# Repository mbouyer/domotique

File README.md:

# domotique
gestion du chauffage et aération d'une habitation

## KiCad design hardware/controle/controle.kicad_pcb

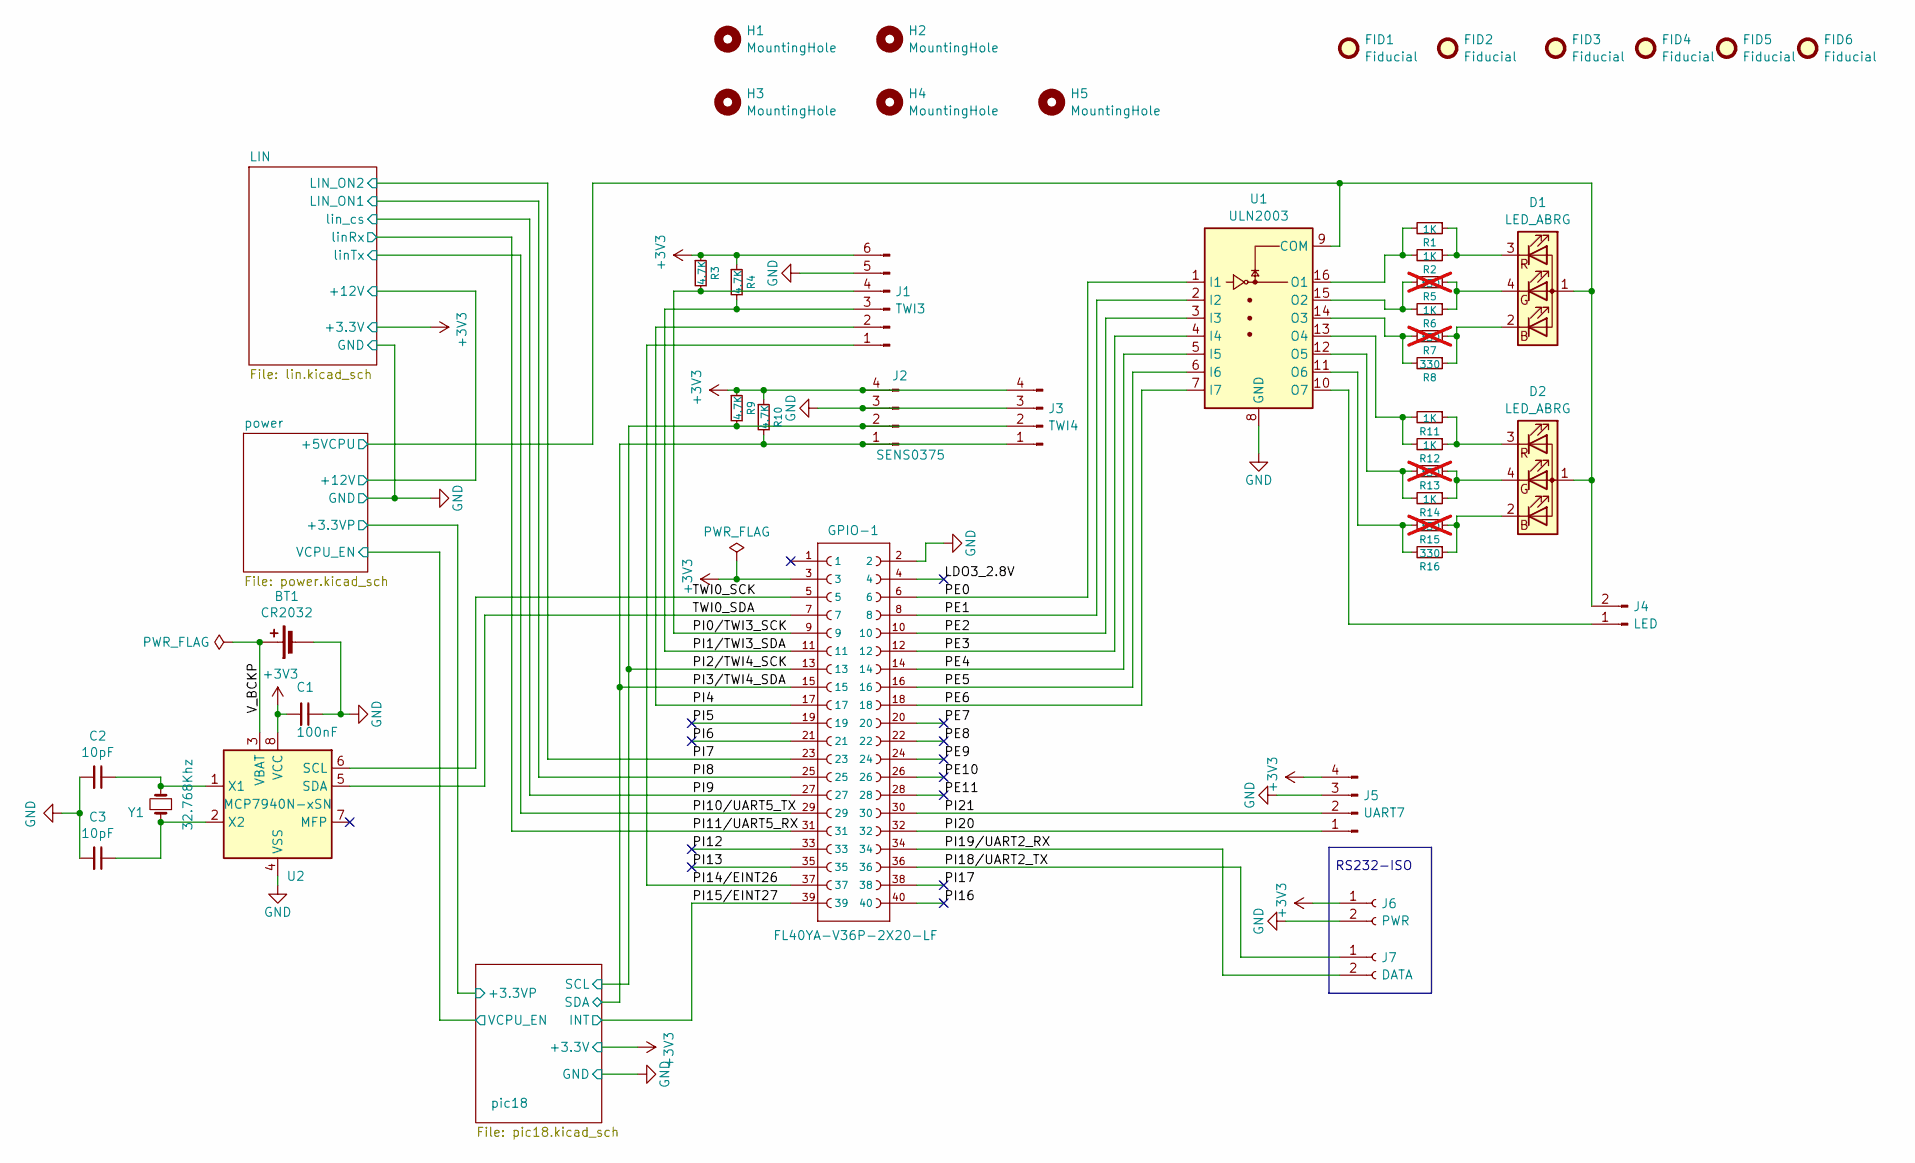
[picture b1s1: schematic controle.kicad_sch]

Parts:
BT1: CR2032; 1066
C1: 100nF; C_0603_1608Metric_Pad1.08x0.95mm_HandSolder
C2, C3: 10pF; C_0603_1608Metric_Pad1.08x0.95mm_HandSolder
D1, D2: LED_ABRG; LED MP001251
FID1, FID2, FID3, FID4, FID5, FID6: Fiducial; Fiducial_1mm_Mask2mm
GPIO-1: FL40YA-V36P-2X20-LF; A10_OLIMEXINO_LIME_SHIELD_1-YA-V36P-2X20-LF
H1, H2, H3, H4, H5: MountingHole; MountingHole_3.2mm_M3
J1: TWI3; PinHeader_1x06_P2.54mm_Vertical
J2: SENS0375; PinHeader_1x04_P2.54mm_Vertical
J3: TWI4; PinHeader_1x04_P2.54mm_Vertical
J4: LED; PinHeader_1x02_P2.54mm_Vertical
J5: UART7; PinHeader_1x04_P2.54mm_Vertical
J6: PWR; PinSocket_1x02_P2.54mm_Vertical
J7: DATA; PinSocket_1x02_P2.54mm_Vertical
R1, R2, R6, R11, R12, R14: 1K; R_0805_2012Metric_Pad1.20x1.40mm_HandSolder
R3, R4, R9, R10: 4.7K; R_0805_2012Metric_Pad1.20x1.40mm_HandSolder
R5, R7, R13, R15: 330; R_0805_2012Metric_Pad1.20x1.40mm_HandSolder; not fitted
R8, R16: 330; R_0805_2012Metric_Pad1.20x1.40mm_HandSolder
U1: ULN2003; SOIC-16_3.9x9.9mm_P1.27mm
U2: MCP7940N-xSN; SOIC-8_3.9x4.9mm_P1.27mm
Y1: 32.768Khz; CMR200T

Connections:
+3V3: C1.2, GPIO-1.3, J1.6, J2.4, J3.4, J5.4, J6.1, R3.1, R4.1, R9.1, R10.1, U2.8 (VCC); also elsewhere on the board
/LDO3_2.8V: GPIO-1.4
/PE0: GPIO-1.6, U1.1 (I1)
/PE1: GPIO-1.8, U1.2 (I2)
/PE2: GPIO-1.10, U1.3 (I3)
/PE3: GPIO-1.12, U1.4 (I4)
/PE4: GPIO-1.14, U1.5 (I5)
/PE5: GPIO-1.16, U1.6 (I6)
/PE6: GPIO-1.18, U1.7 (I7)
/PE7: GPIO-1.20
/PE8: GPIO-1.22
/PE9: GPIO-1.24
/PE10: GPIO-1.26
/PE11: GPIO-1.28
/PI0/TWI3_SCK: GPIO-1.9, J1.4, R3.2
/PI1/TWI3_SDA: GPIO-1.11, J1.3, R4.2
/PI2/TWI4_SCK: GPIO-1.13, J2.2, J3.2, R9.2; also elsewhere on the board
/PI3/TWI4_SDA: GPIO-1.15, J2.1, J3.1, R10.2; also elsewhere on the board
/PI4: GPIO-1.17, J1.2
/PI5: GPIO-1.19
/PI6: GPIO-1.21
/PI7: GPIO-1.23; also elsewhere on the board
/PI8: GPIO-1.25; also elsewhere on the board
/PI9: GPIO-1.27; also elsewhere on the board
/PI10/UART5_TX: GPIO-1.29; also elsewhere on the board
/PI11/UART5_RX: GPIO-1.31; also elsewhere on the board
/PI12: GPIO-1.33
/PI13: GPIO-1.35
/PI14/EINT26: GPIO-1.37, J1.1
/PI15/EINT27: GPIO-1.39; also elsewhere on the board
/PI16: GPIO-1.40
/PI17: GPIO-1.38
/PI18/UART2_TX: GPIO-1.36, J7.1
/PI19/UART2_RX: GPIO-1.34, J7.2
/PI20: GPIO-1.32, J5.1
/PI21: GPIO-1.30, J5.2
/TWI0_SCK: GPIO-1.5, U2.6 (SCL)
/TWI0_SDA: GPIO-1.7, U2.5 (SDA)
/V_BCKP: BT1.1 (+), U2.3 (VBAT)
/power/+5VCPU: D1.1 (A), D2.1 (A), J4.2, U1.9 (COM); also elsewhere on the board
GND: BT1.2 (-), C1.1, C2.2, C3.2, GPIO-1.2, J1.5, J2.3, J3.3, J5.3, J6.2, U1.8 (GND), U2.4 (VSS); also elsewhere on the board
unnamed: D1.2 (BK), R7.1, R8.1
unnamed: D1.4 (GK), R5.1, R6.1
unnamed: D1.3 (RK), R1.1, R2.1
unnamed: D2.2 (BK), R15.1, R16.1
unnamed: D2.4 (GK), R13.1, R14.1
unnamed: D2.3 (RK), R11.1, R12.1
unnamed: J4.1, U1.10 (O7)
unnamed: R1.2, R2.2, U1.16 (O1)
unnamed: R5.2, R6.2, U1.15 (O2)
unnamed: R7.2, R8.2, U1.14 (O3)
unnamed: R11.2, R12.2, U1.13 (O4)
unnamed: R13.2, R14.2, U1.12 (O5)
unnamed: R15.2, R16.2, U1.11 (O6)
unnamed: C2.1, U2.1 (X1), Y1.2
unnamed: C3.1, U2.2 (X2), Y1.1

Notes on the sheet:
RS232-ISO

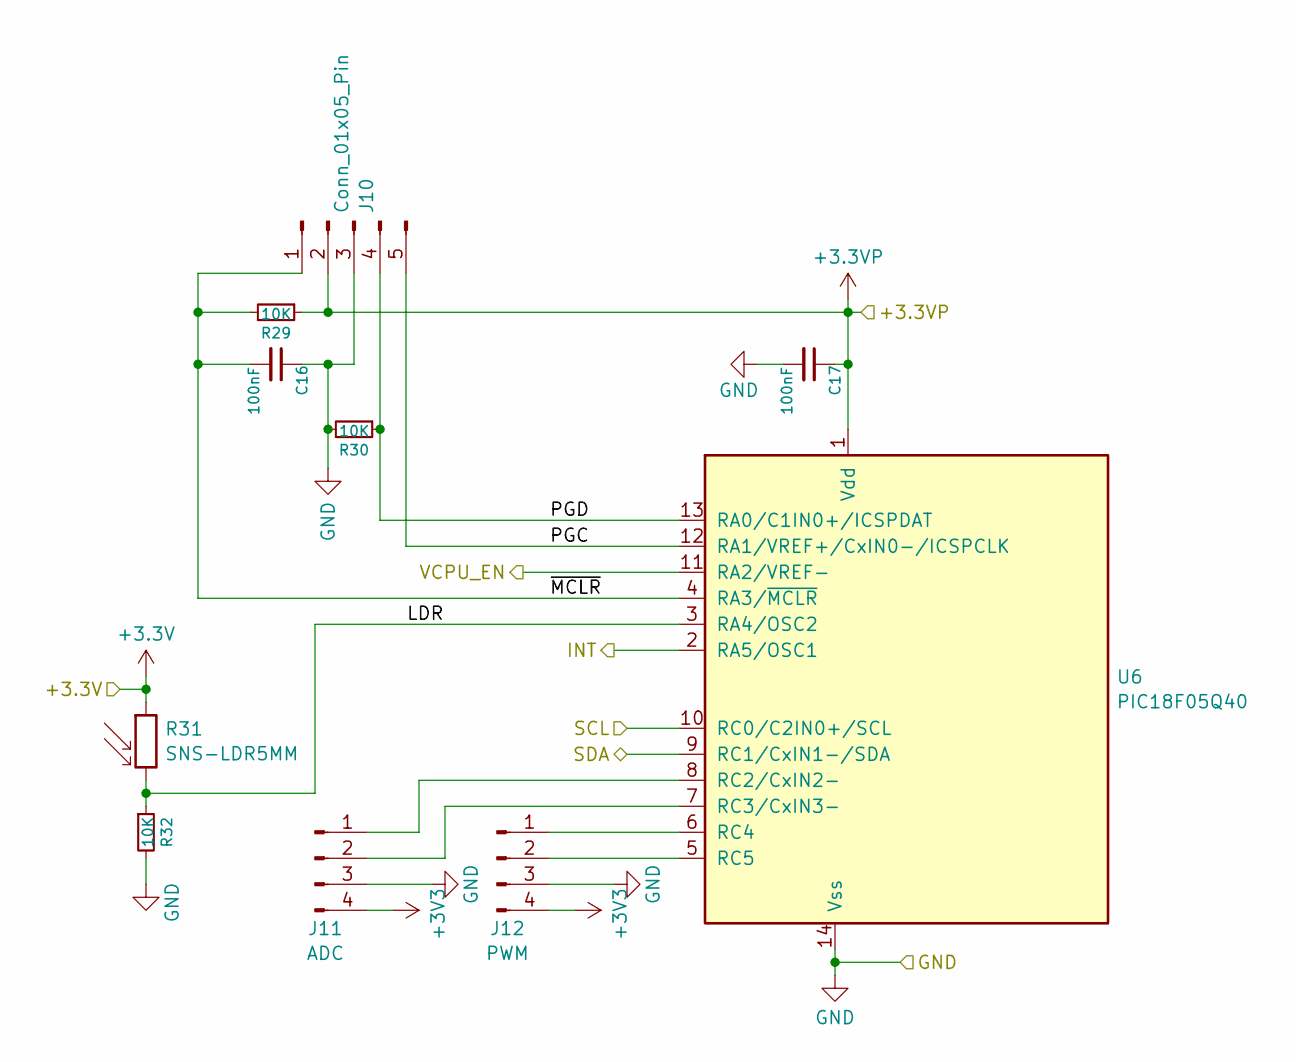
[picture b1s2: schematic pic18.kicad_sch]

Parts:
C16, C17: 100nF; C_0603_1608Metric_Pad1.08x0.95mm_HandSolder
J10: Conn_01x05_Pin; PinHeader_1x05_P2.54mm_Horizontal
J11: ADC; PinHeader_1x04_P2.54mm_Vertical
J12: PWM; PinHeader_1x04_P2.54mm_Vertical
R29, R30, R32: 10K; R_0805_2012Metric_Pad1.20x1.40mm_HandSolder
R31: SNS-LDR5MM; R_LDR_5.0x4.1mm_P3mm_Vertical
U6: PIC18F05Q40; SOIC-14_3.9x8.7mm_P1.27mm

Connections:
+3.3VP: C17.1, J10.2, R29.1, U6.1 (Vdd); also elsewhere on the board
+3V3: J11.4, J12.4, R31.1; also elsewhere on the board
/PI2/TWI4_SCK: U6.10 (RC0/C2IN0+/SCL); also elsewhere on the board
/PI3/TWI4_SDA: U6.9 (RC1/CxIN1-/SDA); also elsewhere on the board
/PI15/EINT27: U6.2 (RA5/OSC1); also elsewhere on the board
/pic18/LDR: R31.2, R32.1, U6.3 (RA4/OSC2)
/pic18/PGC: J10.5, U6.12 (RA1/VREF+/CxIN0-/ICSPCLK)
/pic18/PGD: J10.4, R30.1, U6.13 (RA0/C1IN0+/ICSPDAT)
/pic18/VCPU_EN: U6.11 (RA2/VREF-); also elsewhere on the board
/pic18/~MCLR: C16.2, J10.1, R29.2, U6.4 (RA3/~MCLR)
GND: C16.1, C17.2, J10.3, J11.3, J12.3, R30.2, R32.2, U6.14 (Vss); also elsewhere on the board
unnamed: J11.1, U6.8 (RC2/CxIN2-)
unnamed: J11.2, U6.7 (RC3/CxIN3-)
unnamed: J12.1, U6.6 (RC4)
unnamed: J12.2, U6.5 (RC5)

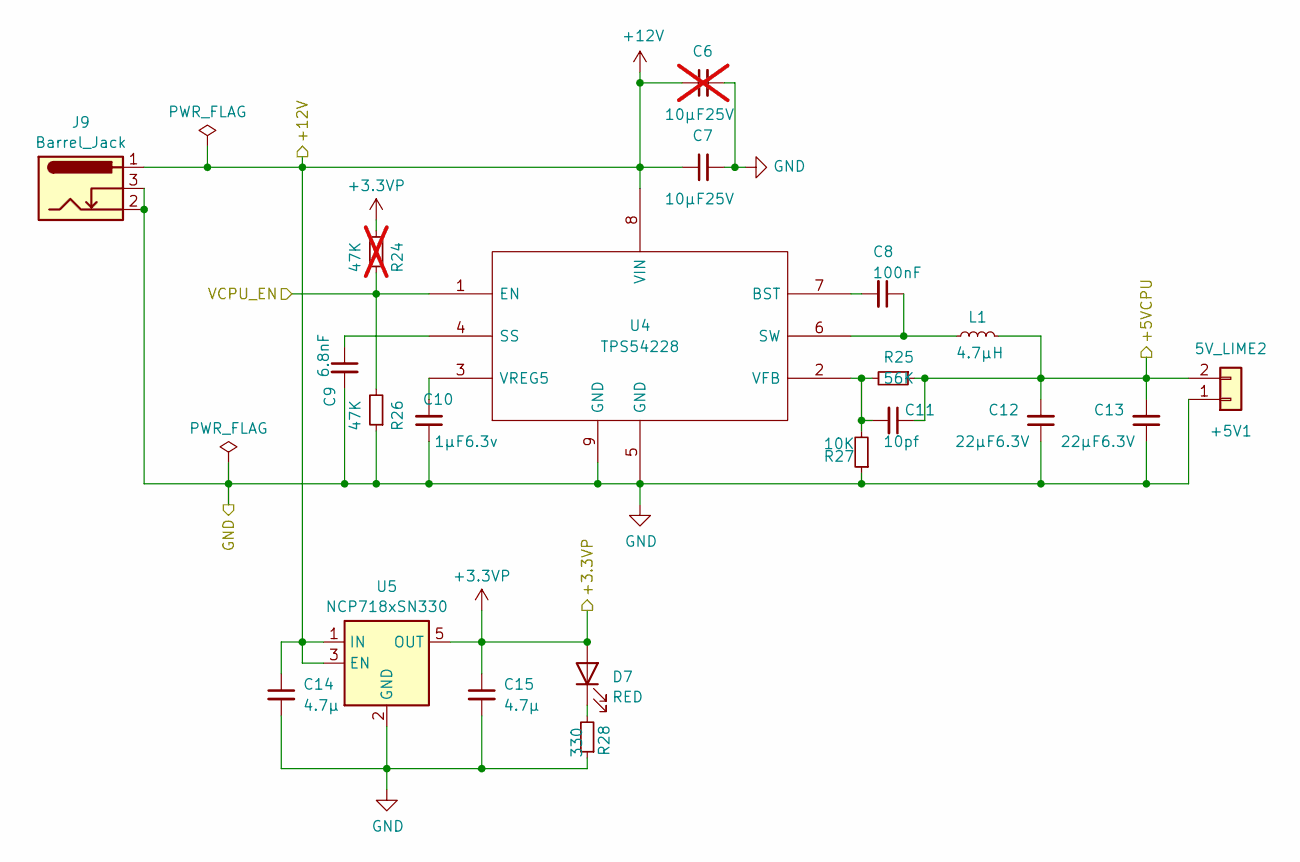
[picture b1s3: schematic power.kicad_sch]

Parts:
+5V1: 5V_LIME2; MC24356
C6: 10µF25V; C_1210_3225Metric_Pad1.33x2.70mm_HandSolder; not fitted
C7: 10µF25V; C_1210_3225Metric_Pad1.33x2.70mm_HandSolder
C8: 100nF; C_0603_1608Metric_Pad1.08x0.95mm_HandSolder
C9: 6.8nF; C_0603_1608Metric_Pad1.08x0.95mm_HandSolder
C10: 1µF6.3v; C_0603_1608Metric_Pad1.08x0.95mm_HandSolder
C11: 10pf; C_0603_1608Metric_Pad1.08x0.95mm_HandSolder
C12, C13: 22µF6.3V; C_1210_3225Metric_Pad1.33x2.70mm_HandSolder
C14, C15: 4.7µ; C_0805_2012Metric_Pad1.18x1.45mm_HandSolder
D7: RED; LED_0805_2012Metric
J9: Barrel_Jack; BarrelJack_Wuerth_6941xx301002
L1: 4.7µH; L_TT_7.3x6.8
R24: 47K; R_0805_2012Metric_Pad1.20x1.40mm_HandSolder; not fitted
R25: 56K; R_0805_2012Metric_Pad1.20x1.40mm_HandSolder
R26: 47K; R_0805_2012Metric_Pad1.20x1.40mm_HandSolder
R27: 10K; R_0805_2012Metric_Pad1.20x1.40mm_HandSolder
R28: 330; R_0805_2012Metric_Pad1.20x1.40mm_HandSolder
U4: TPS54228; SOIC-8-1EP_3.9x4.9mm_P1.27mm_EP2.41x3.3mm
U5: NCP718xSN330; SOT-23-5

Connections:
+3.3VP: C15.1, D7.2 (A), R24.2, U5.5 (OUT); also elsewhere on the board
+12V: C6.1, C7.1, C14.1, J9.1, U4.8 (VIN), U5.1 (IN), U5.3 (EN); also elsewhere on the board
/pic18/VCPU_EN: R24.1, R26.2, U4.1 (EN); also elsewhere on the board
/power/+5VCPU: +5V1.2, C11.1, C12.2, C13.2, L1.2, R25.1; also elsewhere on the board
GND: +5V1.1, C6.2, C7.2, C9.2, C10.1, C12.1, C13.1, C14.2, C15.2, J9.2, J9.3, R26.1, R27.1, R28.1, U4.5 (GND), U4.9 (GND), U5.2 (GND); also elsewhere on the board
unnamed: D7.1 (K), R28.2
unnamed: C8.2, U4.7 (BST)
unnamed: C9.1, U4.4 (SS)
unnamed: C8.1, L1.1, U4.6 (SW)
unnamed: C11.2, R25.2, R27.2, U4.2 (VFB)
unnamed: C10.2, U4.3 (VREG5)

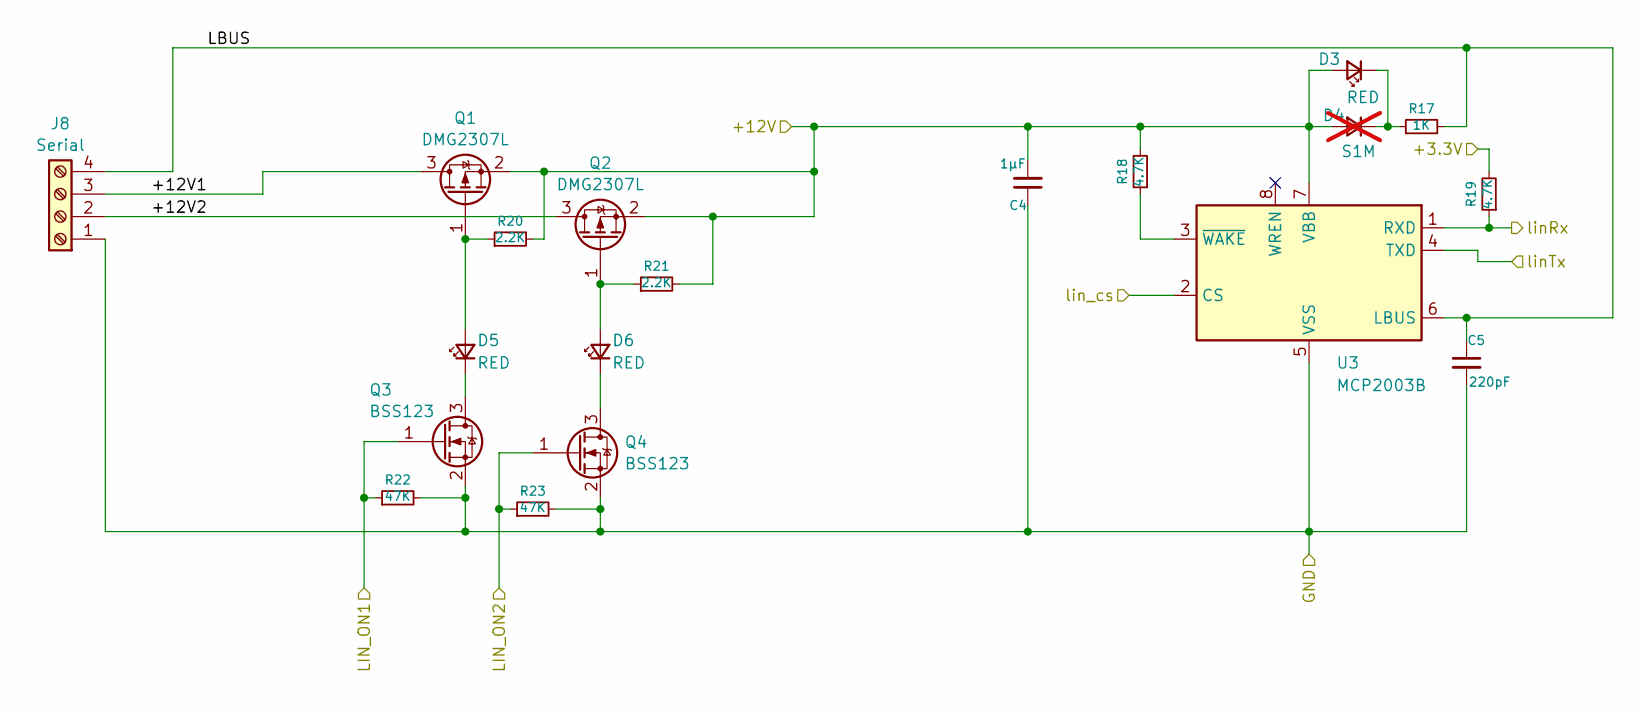
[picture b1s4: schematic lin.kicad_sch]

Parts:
C4: 1µF; C_0805_2012Metric_Pad1.18x1.45mm_HandSolder
C5: 220pF; C_0603_1608Metric_Pad1.08x0.95mm_HandSolder
D3, D5, D6: RED; LED_0603_1608Metric_Pad1.05x0.95mm_HandSolder
D4: S1M; D_SMA; not fitted
J8: Serial; PhoenixContact_MCV_1,5_4-G-3.5_1x04_P3.50mm_Vertical
Q1, Q2: DMG2307L; SOT-23
Q3, Q4: BSS123; SOT-23
R17: 1K; R_0805_2012Metric_Pad1.20x1.40mm_HandSolder
R18, R19: 4.7K; R_0805_2012Metric_Pad1.20x1.40mm_HandSolder
R20, R21: 2.2K; R_0805_2012Metric_Pad1.20x1.40mm_HandSolder
R22, R23: 47K; R_0805_2012Metric_Pad1.20x1.40mm_HandSolder
U3: MCP2003B; SOIC-8_3.9x4.9mm_P1.27mm

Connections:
+3V3: R19.2; also elsewhere on the board
+12V: C4.2, D3.2 (A), D4.2 (A), Q1.2 (S), Q2.2 (S), R18.2, R20.2, R21.2, U3.7 (VBB); also elsewhere on the board
/LIN/+12V1: J8.3, Q1.3 (D)
/LIN/+12V2: J8.2, Q2.3 (D)
/LIN/LBUS: C5.1, J8.4, R17.2, U3.6 (LBUS)
/PI7: Q4.1 (G), R23.1; also elsewhere on the board
/PI8: Q3.1 (G), R22.1; also elsewhere on the board
/PI9: U3.2 (CS); also elsewhere on the board
/PI10/UART5_TX: U3.4 (TXD); also elsewhere on the board
/PI11/UART5_RX: R19.1, U3.1 (RXD); also elsewhere on the board
GND: C4.1, C5.2, J8.1, Q3.2 (S), Q4.2 (S), R22.2, R23.2, U3.5 (VSS); also elsewhere on the board
unnamed: D3.1 (K), D4.1 (K), R17.1
unnamed: D5.2 (A), Q1.1 (G), R20.1
unnamed: D5.1 (K), Q3.3 (D)
unnamed: D6.2 (A), Q2.1 (G), R21.1
unnamed: D6.1 (K), Q4.3 (D)
unnamed: R18.1, U3.3 (~WAKE)

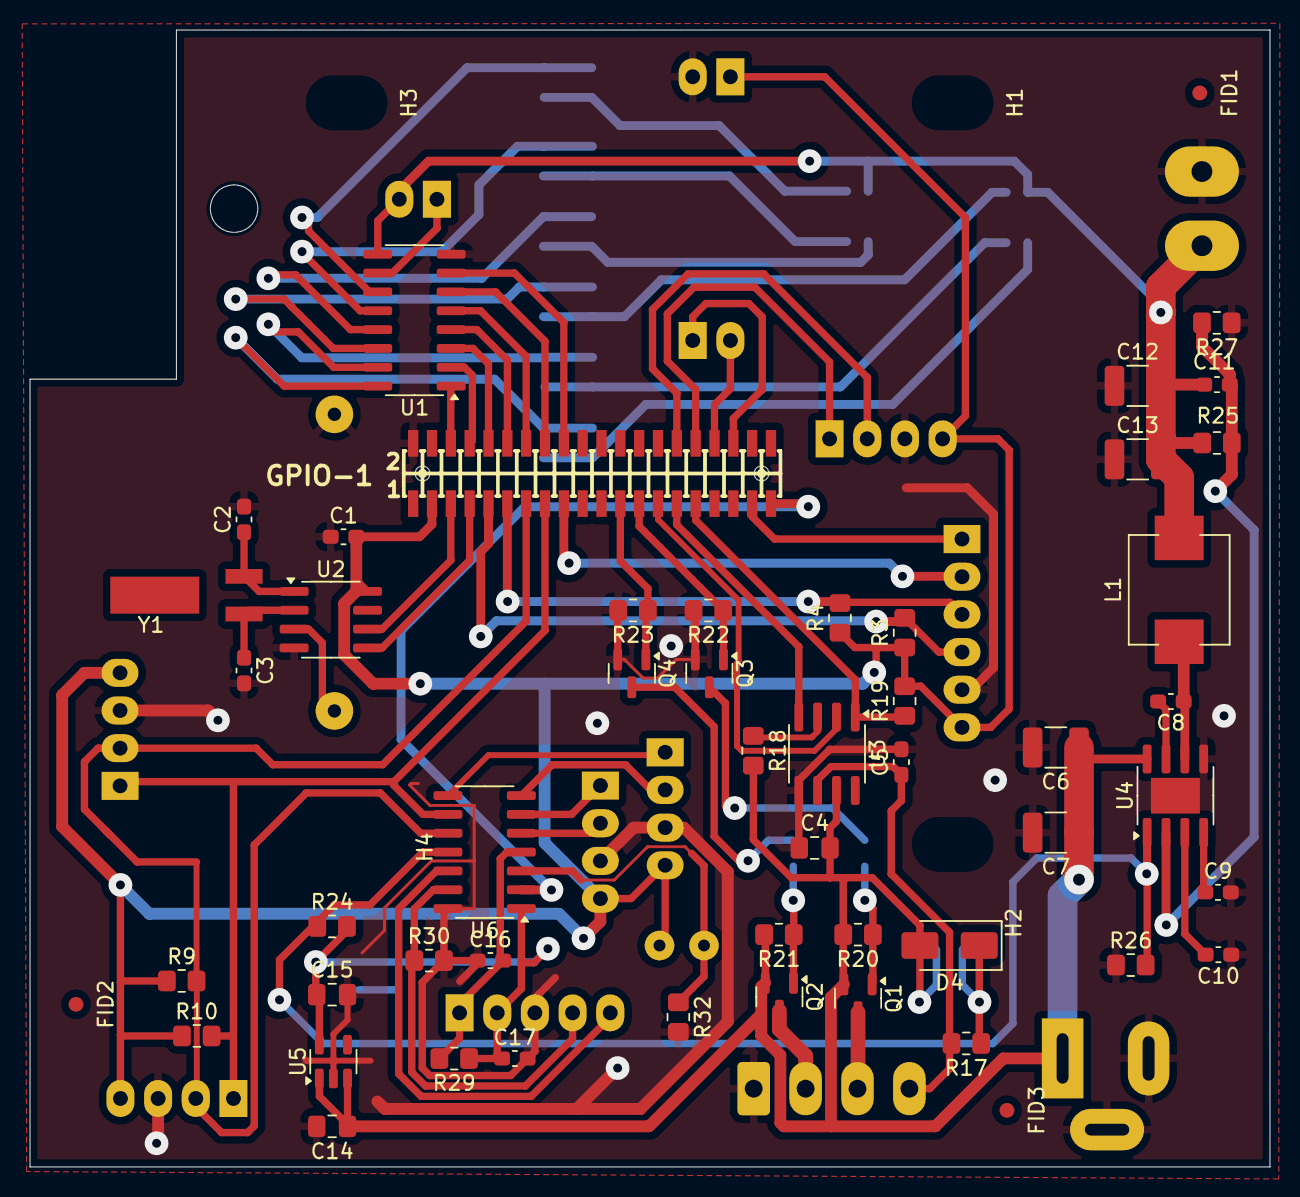
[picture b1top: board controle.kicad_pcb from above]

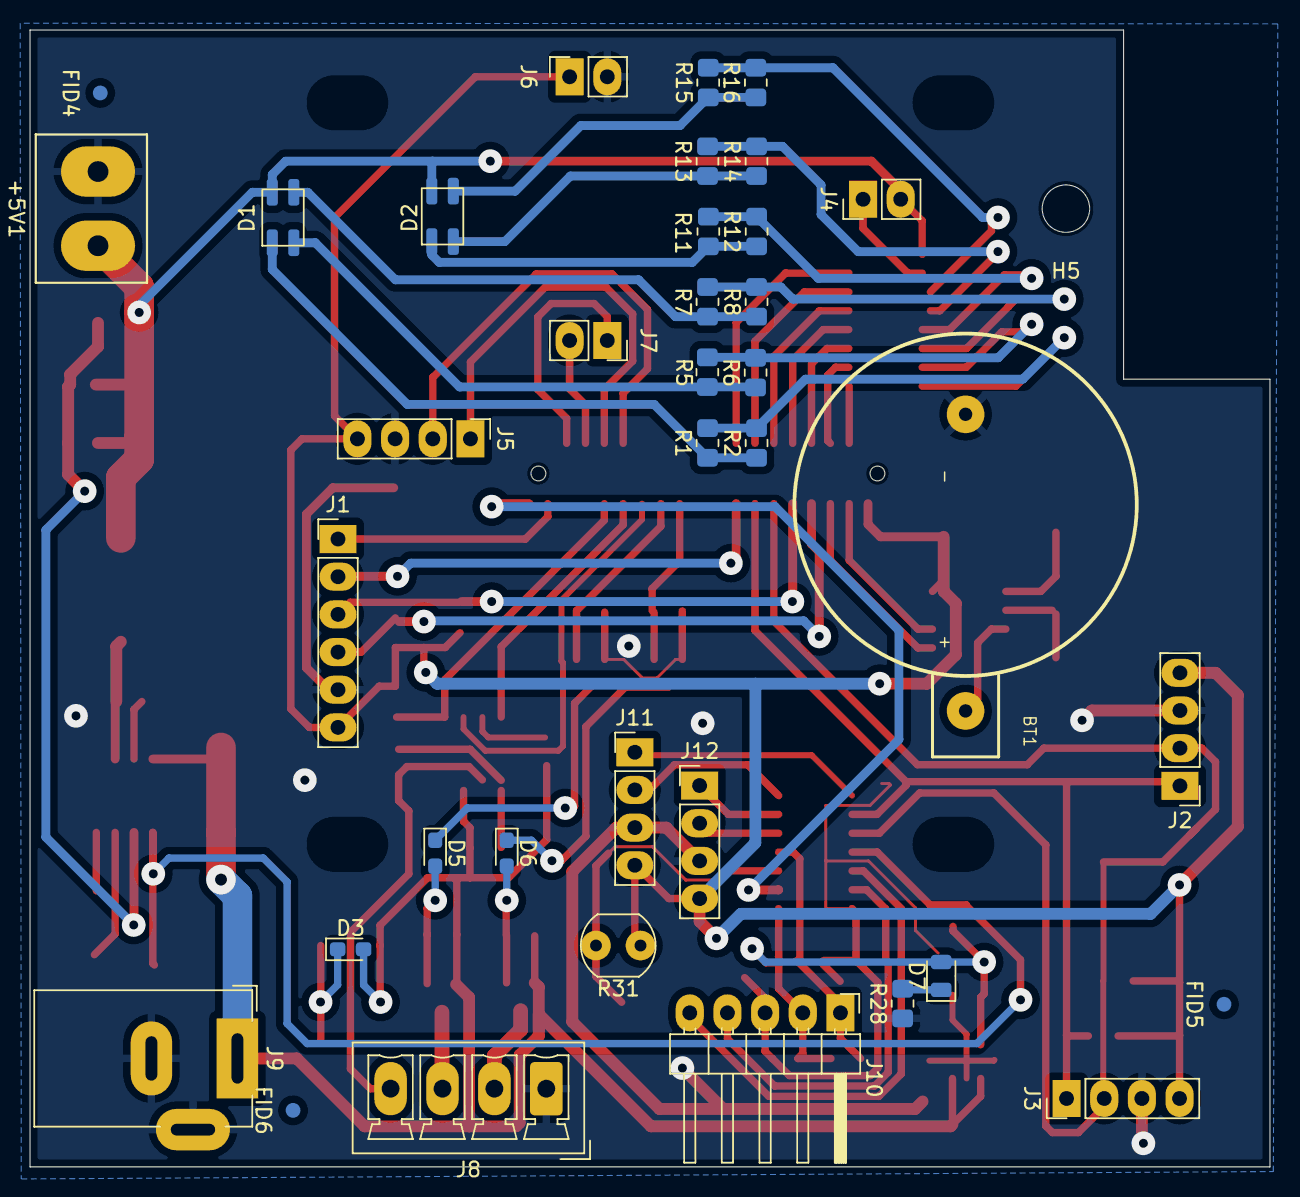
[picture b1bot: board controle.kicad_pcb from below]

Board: 2 copper layers, 83.6 x 76.7 mm, 94 parts (38 on the bottom side), 70 nets.

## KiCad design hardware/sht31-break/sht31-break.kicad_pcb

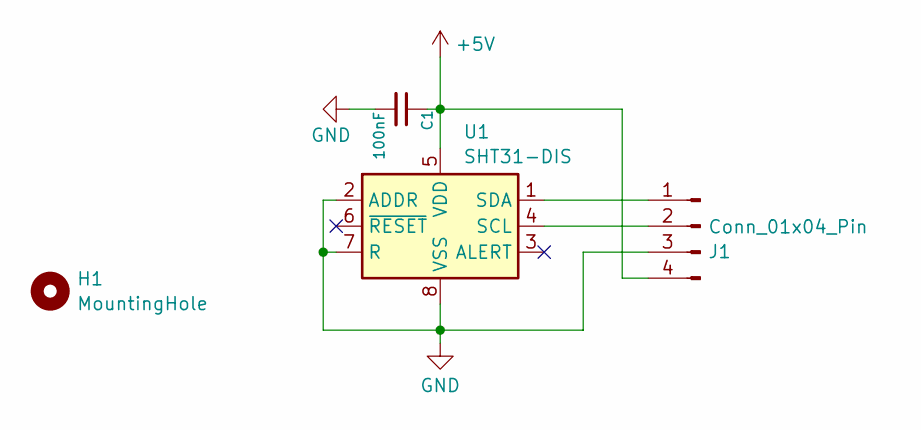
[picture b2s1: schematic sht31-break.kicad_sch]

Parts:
C1: 100nF; C_0603_1608Metric_Pad1.08x0.95mm_HandSolder
H1: MountingHole; MountingHole_3.2mm_M3
J1: Conn_01x04_Pin; SolderWire-0.1sqmm_1x04_P3.6mm_D0.4mm_OD1mm_Relief
U1: SHT31-DIS; Sensirion_DFN-8-1EP_2.5x2.5mm_P0.5mm_EP1.1x1.7mm

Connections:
+5V: C1.1, J1.4, U1.5 (VDD)
GND: C1.2, J1.3, U1.2 (ADDR), U1.7 (R), U1.8 (VSS), U1.9 (VSS)
unnamed: J1.1, U1.1 (SDA)
unnamed: J1.2, U1.4 (SCL)

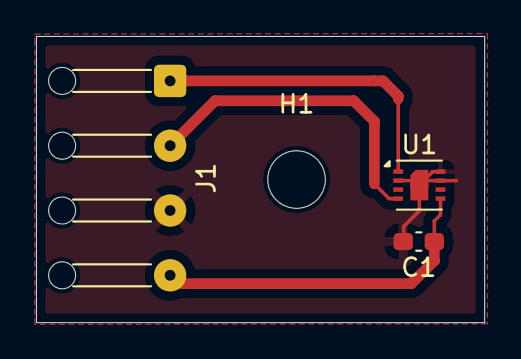
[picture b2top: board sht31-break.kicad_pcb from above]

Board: 2 copper layers, 24.9 x 15.9 mm, 4 parts (0 on the bottom side), 4 nets.

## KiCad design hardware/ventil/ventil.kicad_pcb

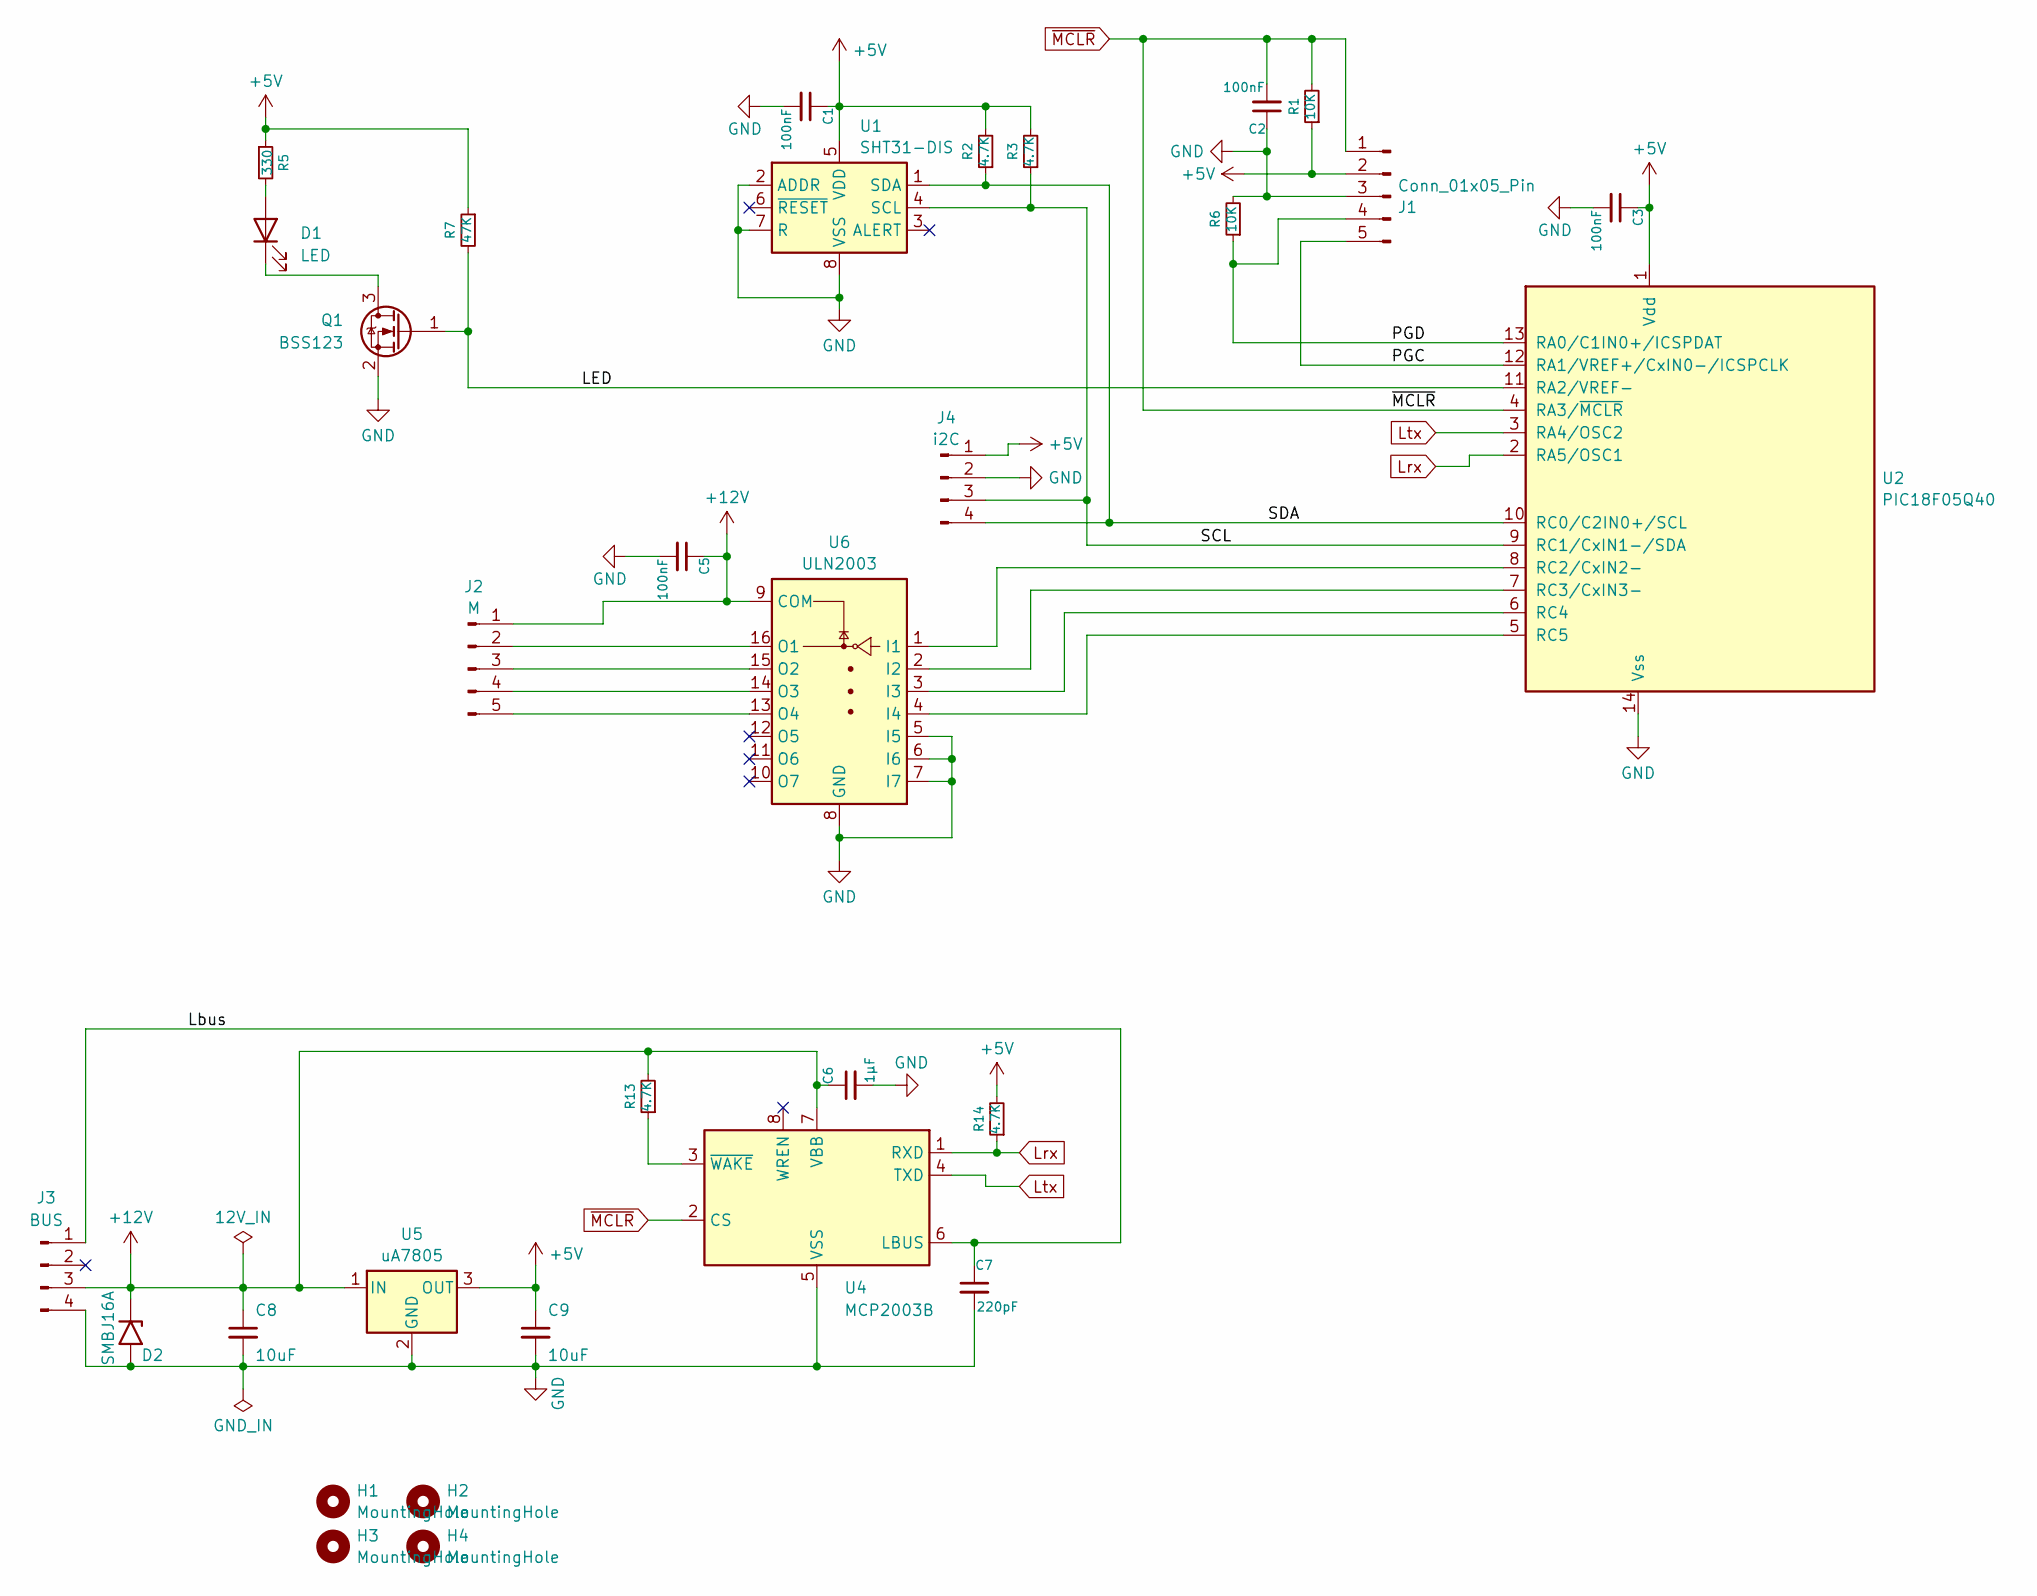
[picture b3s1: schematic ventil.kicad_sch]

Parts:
C1, C2, C3, C5: 100nF; C_0603_1608Metric_Pad1.08x0.95mm_HandSolder
C6: 1µF; C_0805_2012Metric_Pad1.18x1.45mm_HandSolder
C7: 220pF; C_0603_1608Metric_Pad1.08x0.95mm_HandSolder
C8: 10uF; C_1210_3225Metric_Pad1.33x2.70mm_HandSolder
C9: 10uF; C_0805_2012Metric_Pad1.18x1.45mm_HandSolder
D1: LED; LED_0603_1608Metric_Pad1.05x0.95mm_HandSolder
D2: SMBJ16A; D_SMB_Handsoldering
H1, H2, H3, H4: MountingHole; MountingHole_3.2mm_M3
J1: Conn_01x05_Pin; Molex_Pico-SPOX-5-Vertical
J2: M; JST_XH_S5B-XH-A_1x05_P2.50mm_Horizontal
J3: BUS; Molex Pico-SPOX-4_90
J4: i2C; Molex Pico-SPOX-4_90
Q1: BSS123; SOT-23
R1, R6: 10K; R_0805_2012Metric_Pad1.20x1.40mm_HandSolder
R2, R3, R13, R14: 4.7K; R_0805_2012Metric_Pad1.20x1.40mm_HandSolder
R5: 330; R_0805_2012Metric_Pad1.20x1.40mm_HandSolder
R7: 47K; R_0805_2012Metric_Pad1.20x1.40mm_HandSolder
U1: SHT31-DIS; Sensirion_DFN-8-1EP_2.5x2.5mm_P0.5mm_EP1.1x1.7mm
U2: PIC18F05Q40; SOIC-14_3.9x8.7mm_P1.27mm
U4: MCP2003B; SOIC-8_3.9x4.9mm_P1.27mm
U5: uA7805; TO-252-3_TabPin2
U6: ULN2003; SOIC-16_3.9x9.9mm_P1.27mm

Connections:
+5V: C1.1, C3.1, C9.1, J1.2, J4.1, R1.1, R2.2, R3.2, R5.1, R7.1, R14.2, U1.5 (VDD), U2.1 (Vdd), U5.3 (OUT)
+12V: C5.1, C6.1, C8.1, D2.1 (A1), J2.1, J3.3, R13.2, U4.7 (VBB), U5.1 (IN), U6.9 (COM)
/LED: Q1.1 (G), R7.2, U2.11 (RA2/VREF-)
/Lbus: C7.1, J3.1, U4.6 (LBUS)
/PGC: J1.5, U2.12 (RA1/VREF+/CxIN0-/ICSPCLK)
/PGD: J1.4, R6.1, U2.13 (RA0/C1IN0+/ICSPDAT)
/SCL: J4.3, R3.1, U1.4 (SCL), U2.9 (RC1/CxIN1-/SDA)
/SDA: J4.4, R2.1, U1.1 (SDA), U2.10 (RC0/C2IN0+/SCL)
GND: C1.2, C2.1, C3.2, C5.2, C6.2, C7.2, C8.2, C9.2, D2.2 (A2), J1.3, J3.4, J4.2, Q1.2 (S), R6.2, U1.2 (ADDR), U1.7 (R), U1.8 (VSS), U1.9 (VSS), U2.14 (Vss), U4.5 (VSS), U5.2 (GND), U6.5 (I5), U6.6 (I6), U6.7 (I7), U6.8 (GND)
Lrx: R14.1, U2.2 (RA5/OSC1), U4.1 (RXD)
Ltx: U2.3 (RA4/OSC2), U4.4 (TXD)
unnamed: D1.2 (A), R5.2
unnamed: D1.1 (K), Q1.3 (D)
unnamed: J2.2, U6.16 (O1)
unnamed: J2.3, U6.15 (O2)
unnamed: J2.4, U6.14 (O3)
unnamed: J2.5, U6.13 (O4)
unnamed: U2.8 (RC2/CxIN2-), U6.1 (I1)
unnamed: U2.7 (RC3/CxIN3-), U6.2 (I2)
unnamed: U2.6 (RC4), U6.3 (I3)
unnamed: U2.5 (RC5), U6.4 (I4)
unnamed: R13.1, U4.3 (~WAKE)
~MCLR: C2.2, J1.1, R1.2, U2.4 (RA3/~MCLR), U4.2 (CS)

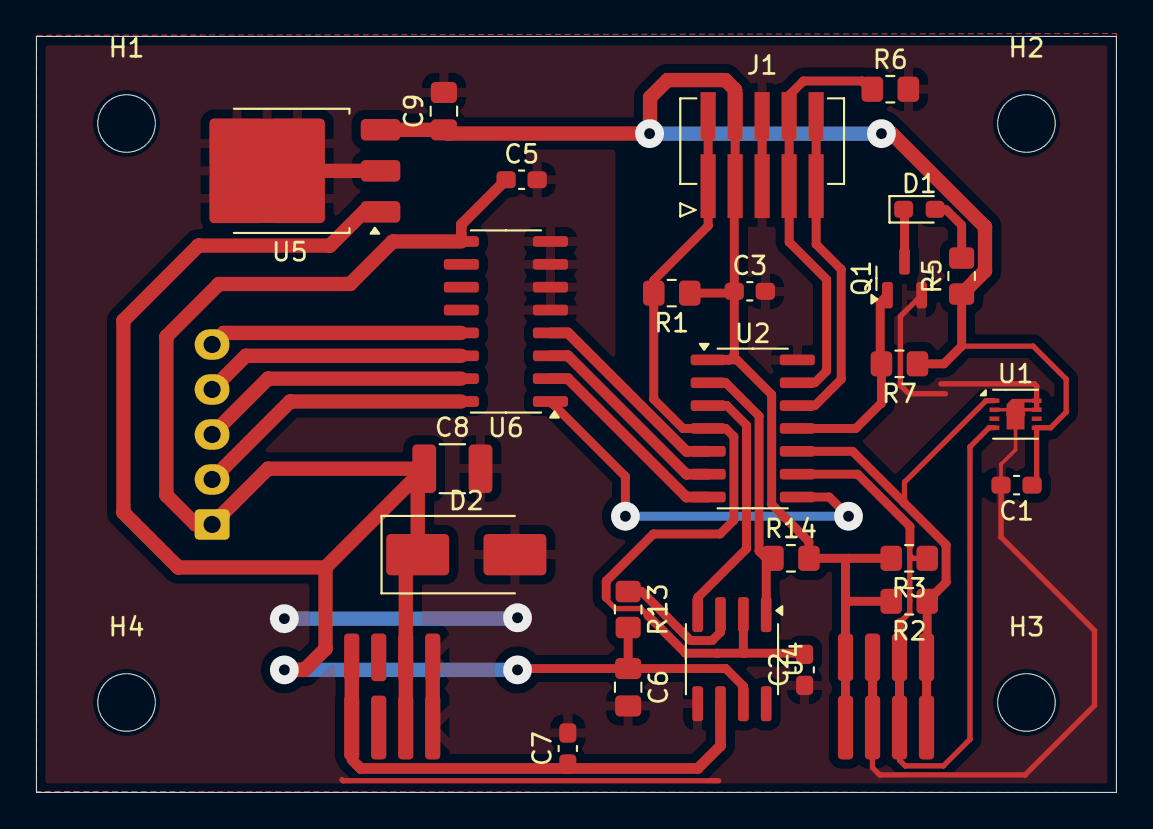
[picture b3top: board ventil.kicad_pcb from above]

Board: 2 copper layers, 60.0 x 42.0 mm, 32 parts (1 on the bottom side), 23 nets.

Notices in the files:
software/ventil/main.c:
Copyright (c) 2025 Manuel Bouyer
All rights reserved.
